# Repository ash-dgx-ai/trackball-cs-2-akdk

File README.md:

# trackball-cs-2

Generated by [Auto-Keyboard-Design-Kit](https://auto-kdk.pages.dev/)

## Preview

- 3D View

- Top View

## Parts List

|Part|Quantity|
|---|---|
|wireless controller|2|
|Conthrough(2.5mm, 9pin)|4|
|Battery|2|
USB-C cable|1|
|MX switch and MX socket|34|
|Diode|34|
|Keycap|34|

## Controller board (reverse-engineered)

The wireless controller board is not included in the original Auto-KDK output.
A reverse-engineered KiCad design compatible with this keyboard is in
[`controller-kicad/`](controller-kicad/README.md).

- 98.0 x 29.0 mm, 2-layer, bottom-side assembly
- Ebyte E73-2G4M08S1C (JLCPCB C356849), MCP73831 4.2V charger, USB-C, PH battery
  connector, trackball FFC, DPDT power switch
- JLCPCB Gerbers/BOM/CPL are included in `controller-kicad/`
- Flash the Adafruit nRF52 UF2 bootloader via the solderless 6-pin 2.54 mm pogo test pads (J4) before use.
- The blank E73 starts at 1.8 V (REGOUT0 default); use a VTref-sensing or level-shifted probe for the first SWD write.

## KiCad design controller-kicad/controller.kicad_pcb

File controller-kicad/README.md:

# AKDK-compatible wireless controller board

Reverse-engineered from the `trackball-cs-2-akdk` repository data
(main-PCB controller footprint, case STL, ZMK `akdk_bt1` DTS, and the
Auto-KDK README).

## Board

- Size: 98.0 x 29.0 mm
- 2 layers, 1.6 mm thickness
- All components are on the **bottom side** (the side opposite the
  conthrough pads). Order JLCPCB PCBA with **Bottom side** assembly.
- Conthrough pads: 2 x 9, 1.27 mm pitch, 19.0 mm row spacing, on the top side.

### Conthrough (KONSHU / コンスルー) mounting

The Conthrough used by this project is the 9-pin, 1.27 mm pitch, H2.5 mm
**through-hole** type (コンスルー 9ピン, 1.27 mm, 高さ2.5 mm). J5 is a 2 x 9
plated-through-hole footprint (0.7 mm drill, 1.1 mm pad, 1.27 mm pitch,
19.0 mm between rows) on the top side. Solder the Conthrough pins into these
holes.

- Hole/pad geometry: 0.7 mm finished hole, 1.1 mm pad, 1.27 mm pitch, 19.0 mm
  row spacing. The 1.1 mm pad leaves 0.17 mm between adjacent pads, above the
  0.1 mm clearance used by this board.
- The pads are plated through-holes, so the Conthrough is mechanically strong.
  Solder on the bottom side (all other components are also on the bottom).
- J5 is excluded from the JLCPCB BOM/CPL; it is a mechanical part. The board
  itself is ordered with the through-holes, so no extra drilling is needed.
- Board thickness is 1.6 mm. Conthrough H2.5 mm is designed for a 1.6 mm board
  plus a 0.9 mm gap; verify the gap to the main PCB after assembly.
- USB-C: 30.85 mm from the left edge, on the top edge. The left case opening
  is centred at x = -18.25 mm, z = -5.75 mm; the connector is horizontally
  centred in the opening. The 3D check shows the connector top is about
  0.17 mm above the case opening top; sand the opening by ~0.2 mm or lower the
  board by ~0.2 mm if it is tight.
- USB-C data: both plug orientations are supported. A6/B6 (D+) and A7/B7
  (D-) are tied with 0.4/0.2 mm via-in-pad and short F.Cu bridges. USB_DM is
  routed manually on F.Cu because Freerouting could not fit both data nets in
  the available corridor. Power, CC and charging also work in both
  orientations. The data vias are inside the 0.3 mm pads; see the JLCPCB
  via-in-pad note below.
- The same board is used for the right half by flipping it over (the main PCB
  SIDE1/SIDE2 variants are different net assignments, not different boards).

## Power / charger

- Li-Po 1S, 3.7 V, with protection circuit, PH 2-pin connector.
- MCP73831 4.2 V single-cell charger (LCSC C14879), 6.2 k PROG resistor
  (~160 mA). The TP4057 was replaced because its 4.24 V termination is above
  the usual 4.20 V Li-Po limit. The charger footprint is a 5-pad SOT-23-5 land
  pattern; PROG is pad 5.
- Charger bypass capacitors: C6/C8 = 10 uF each on VBUS and C7/C9 = 10 uF
  each on VBAT (LCSC C19702, 0603, 10 V), i.e. 20 uF nominal per rail.
  This meets the MCP73831 4.7 uF recommendation even after DC-bias derating;
  verify the effective value at 5 V/4.2 V. C7/C9 are connected to VBAT with
  short B.Cu traces. C8 is at (37.0, 1.8) and C9 at (32.4, 10.0).
- Power switch: DPDT. OFF grounds P0.13 and disconnects the battery; USB then
  powers VDDH through a Schottky diode. Grounding P0.13 is the DFU pin only on
  bootloader builds that use it; see the bootloader section.
- The E73 runs in **high-voltage mode**: VDDH is fed from the battery/USB
  through the Schottky diodes (D1/D2), and VDD is the module's internal 3.3 V
  LDO output (DC/DC disabled, DCCH unconnected). VDD and VDDH are **not**
  tied together on the board; the 3V3 rail is the module's VDD output.
- Battery polarity: J2 pin 1 = +, pin 2 = -. Verify the battery lead polarity
  before plugging it in.
- C3 is 4.7 uF (LCSC C19666, 0603 16 V) on the 3V3/VDD rail. The nRF52840
  VDD decoupling target is 2.7-5.5 uF effective including the E73 module's
  internal capacitors; C3 alone is not the whole sum. Verify the total with
  the E73 module data.
- A blank E73 has REGOUT0 = 1.8 V, so VDD (the 3V3 rail) is 1.8 V until the
  UICR is programmed. After the bootloader/firmware sets REGOUT0 to 3.3 V,
  verify 3.3 V on C3 before connecting the trackball FFC.
- **Battery operation / REG0 dropout**: VDDH = VBAT minus the D2 Schottky
  drop. REG0 regulates 3.3 V only while VDDH is at least about 3.6 V; below
  that it is in dropout and the 3V3 rail follows VDDH (roughly 2.6-3.0 V at
  the battery cutoff). The nRF52840 itself remains within its 1.8-3.6 V
  supply range, and the trackball module's 1.8 V sensor supply should remain
  in regulation, but the 3.3 V rail is not regulated. Measure VDDH/VDD at the
  battery low-voltage cutoff and check the trackball module's minimum VDDIO.
  If the module requires a regulated 3.3 V, add a boost converter (or use a
  higher-voltage supply); otherwise the existing high-voltage/LDO mode is
  acceptable.
- **External 3V3 load**: in high-voltage mode the nRF52840 can supply only
  about 25 mA externally at <=4 dBm (5 mA above 4 dBm, 1 mA in System OFF).
  Measure the trackball module's worst-case current. If it exceeds 25 mA, or
  a regulated 3.3 V is required, add an independent 3.3 V regulator; do not
  rely on the E73 VDD output alone.

## Trackball FFC

The controller-side FFC connector is on the bottom side, while the trackball
module connector is on the opposite side. With a same-side FFC cable the pin
order is reversed. The controller board uses:

| Controller FFC pin | Signal |
|---|---|
| 1 | GND |
| 2 | SCLK (P0.12) |
| 3 | SDIO (P1.09) |
| 4 | MOTION (P0.15) |
| 5 | CS (P0.13) |
| 6 | 3.3 V |

The trackball module's own pinout is 1=3.3V, 2=CS, 3=MOTION, 4=SDIO, 5=SCLK,
6=GND. Verify the cable orientation before soldering/plugging.

## Bootloader / firmware

- The board uses the Adafruit nRF52 UF2 bootloader. Flash it once via the
  solderless 6-pin 2.54 mm pogo test pads (J4). No header or extra parts are
  needed.
- **First SWD connection / REGOUT0**: A blank nRF52840/E73 has
  REGOUT0 = 1.8 V, so VDD and the SWD pins are at 1.8 V. A 3.3 V probe can
  overdrive them. Use a debugger with VTref sensing and level shifting, or a
  1.8 V-compatible probe, for the first write. J4 pad 1 is the target VDD
  sense point; do **not** connect the Pico's 3V3 output to it. For a
  Pico-based first write, use a bidirectional level shifter. TXS0102 is
  auto-direction but must be verified at the SWD clock/load. A single
  74LVC2T45 is **not** suitable: its two channels share DIR, while SWCLK is
  one-way and SWDIO is bidirectional. Use two 74LVC1T45 (one per line) or a
  TXS0102 with VCCA = J4 pad 1 (1.8 V) and VCCB = Pico 3V3, common GND. The
  most reliable option is a debugger with native 1.8 V VTref/level shifting.
- Flash a bootloader build that defines `UICR_REGOUT0_VALUE = 3V3` (for
  example the nice_nano or pillbug build). The bootloader sets REGOUT0 and
  resets; verify 3.3 V on C3. If the chosen build does not set REGOUT0,
  program it via SWD/UICR before using 3.3 V logic. After that, the Pico 2 WH
  3.3 V SWD signals are safe.
- Pogo pad mapping (pad 1 is the pad nearest the top edge; the row is on the
  left edge, 5 mm from the board edge, within the 25 mm clip depth):

  | Pogo pad | Signal | Pico 2 WH connection |
  |---|---|---|
  | 1 | VTref (module VDD sense) | debugger VTref; not Pico 3V3 |
  | 2 | SWDIO | GP3 (level-shifted for the first 1.8 V write) |
  | 3 | SWCLK | GP2 (level-shifted for the first 1.8 V write) |
  | 4 | GND | GND |
  | 5 | RESET (P0.18) | optional; not GP4 by default |
  | 6 | GND | GND |

  The Pico H/2 WH runs the `debugprobe` firmware (SWCLK=GPIO2, SWDIO=GPIO3).
  GP4 is not a guaranteed reset output in all debugprobe builds; leave pad 5
  open unless your probe provides a reset output. Use female-female jumper
  wires; the clip clamps the left board edge, and the 2.54 mm pitch pads are
  2.0 mm diameter with 0.54 mm gaps, so adjacent clip pins do not short.
- **DFU entry**: The power switch OFF grounds P0.13, but that is the DFU
  button only on bootloader builds that define `BUTTON_DFU = P0.13`. The
  nice_nano build has no DFU button and uses the 1200-baud touch instead. If
  OFF + USB does not enter UF2, use the 1200-baud touch (or the reset pad)
  rather than assuming P0.13 works.
- The trackball SPI overlay was changed from `nordic,nrf-spim` to
  `nordic,nrf-spi` as a PAW3222 compatibility precaution; verify on hardware.
  The ZMK left/right build and input test are still pending.
- After the bootloader is flashed, copy the ZMK UF2 built from the
  `trackball-cs-2-akdk` repo.
- The E73-2G4M08S1C exposes all GPIOs used by the `akdk_bt1` DTS except P1.15
  (connector pad 17), which is unused by the firmware. No firmware change is
  required for the matrix/trackball mapping. The module runs in high-voltage
  mode with its internal LDO; DCCH is left unconnected as in the E73 reference
  design.

## JLCPCB order

- Gerbers/drill: `controller_gerbers.zip`
- BOM: `jlcpcb_bom.csv`
- CPL: `jlcpcb_cpl.csv`
- PCB: 98 x 29 mm, 2 layers, 1.6 mm, HASL, default solder mask.
- PCBA: **Bottom side**. The BOM includes the JST PH battery connector and the
  ALPS DPDT switch (THT). JLCPCB THT assembly may be available; otherwise
  hand-solder those two parts. The pogo test pads J4 and the conthrough J5 are
  not in the BOM (J4 is bare copper; J5 is a THT mechanical part). The SWD
  pogo connection is solderless, but J5, J2 and SW1 still require soldering.
- All BOM LCSC parts were in stock at the time of writing:
  - C356849 E73-2G4M08S1C (472)
  - C165948 USB-C TYPE-C-31-M-12 (158981)
  - C14879 MCP73831 (4.2 V charger, in stock)
  - C19702 10uF 0603 10V (C6/C7/C8/C9 charger bypass, in stock)
  - C19666 4.7uF 0603 16V (C3 VDD decoupling, in stock)
  - C131337 JST PH 2P (215233)
  - C202118 FH12-6S-0.5SH (2179)
  - C97434 ALPS SSSS820101 DPDT (2131)
  - C2986031 green LED (20891)
  - C2480 SS14 (1713221)
  - C23186 5.1k, C4260 6.2k, C22976 2M, C22935 1M, C21190 1k, C15849 1uF,
    C14663 0.1uF (all basic/stock)
- **Via-in-pad**: the USB-C D+/D- pads still use 0.4/0.2 mm via-in-pad.
  Moving them outside the 0.3 mm pads conflicts with the CC1/CC2 fan-out, so
  the verified geometry is kept. For the 2-layer JLCPCB order, select the
  **Via in Pad** option (resin-filled and copper-capped, IPC-4761 Type VII)
  and confirm the price/availability; if it is unavailable, the USB-C vias
  must be moved. The P1.06 vias have been moved outside the U1/R6 pads, so
  only the USB-C vias need the special process.
- The CPL rotations are KiCad rotations. Check the JLCPCB placement preview;
  bottom-side rotations may need adjustment. The KiCad **Fabrication Toolkit**
  plugin can generate a JLCPCB-ready CPL if desired.

## DRC

- `kicad-cli pcb drc --severity-error`: **0 violations, 0 unconnected pads,
  0 footprint errors**.
- Run `scripts/set_drc_severity.py` after the PCB pipeline: KiCad rewrites
  the project when a board is saved, which resets courtyard overlaps to
  error. The script keeps them as warnings.
- Full-severity DRC still reports non-electrical warnings: 12 courtyard
  overlaps (bounding boxes; check the 3D preview), silkscreen overlaps/
  clipping, and 15 GND stitching vias that connect only to one pour. The
  stitching vias are intentional; they are not electrically dangling. The
  R3/J2 body overlap was fixed by moving R3 to x=40.5 mm. The C7/J1,
  C8/C9/J1 and C2/U1 overlaps are courtyard-only: the USB-C body ends below
  C7/C9, C8 is clear of C6, and C2's body ends at 80.2 mm while the E73 body
  starts at 80.5 mm. C2 pad 1 overlaps the U1 VDDH pad by design (same net).
- The dense routing splits the B.Cu GND pour into islands. `scripts/stitch_zones.py`
  adds GND stitching vias so every island connects to the main GND; run it
  after `patch_pcb.py` when rebuilding. Skipping it leaves the ground pour
  split.
- The pogo test pads J4 are bare copper pads on the top side, 5 mm from the
  left edge, 2.54 mm pitch, 2.0 mm diameter. They are excluded from BOM/CPL.

## Rebuild

Run with the KiCad AppImage Python (see the scripts for the exact paths):

1. `generate_pcb.py`
2. `route_pcb.py` — assigns nets and imports `controller.ses`. The committed
   session is reused by default so the verified routing is reproducible. Set
   `REROUTE=1` to run Freerouting again; after a fresh route, run
   `export_ses.py` to freeze the new session.
3. `finish_pcb.py` — restores GND and adds the copper pours. Do not import the
   SES here again; `route_pcb.py` already did it.
4. `patch_pcb.py` — USB-C D+/D-, LED/P1.06, C7 VBAT, P0.12 stub, GND stitching.
5. `stitch_zones.py` — connects the remaining GND pour islands.
6. `set_drc_severity.py` — keeps courtyard overlaps as warnings before the
   final DRC report.
7. `update_lcsc.py` is optional; it refreshes the LCSC fields from the table
   above (U2=MCP73831/C14879, C6/C7=C19702).

Then run `kicad-cli pcb drc --severity-error`, and export Gerbers/drill,
BOM/CPL, STEP and PDFs with `kicad-cli` and `generate_bom_cpl.py`.

## Files

- `controller.kicad_pcb` — routed PCB
- `controller.kicad_sch` — block-diagram schematic (global-label connections)
- `controller.kicad_pro` — KiCad project
- `controller_gerbers.zip` — Gerbers + drill files
- `jlcpcb_bom.csv`, `jlcpcb_cpl.csv` — JLCPCB PCBA files
- `controller_sch.pdf`, `controller_pcb_front.pdf`, `controller_pcb_back.pdf`
- `controller.step` — 3D model for case/USB verification
- `controller.pretty/MCP73831_SOT-23-5.kicad_mod` — 5-pad charger footprint (PROG=pad 5)
- `controller.3dshapes/SOT-23-5.wrl`, `controller.3dshapes/SOT-23-5.step`
- `scripts/` — generation/route/BOM/DRC scripts

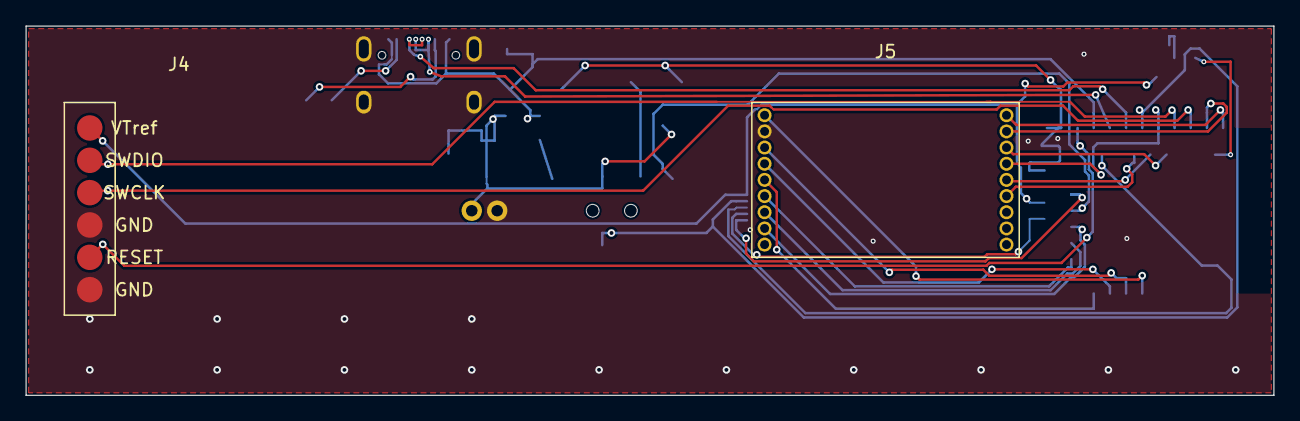
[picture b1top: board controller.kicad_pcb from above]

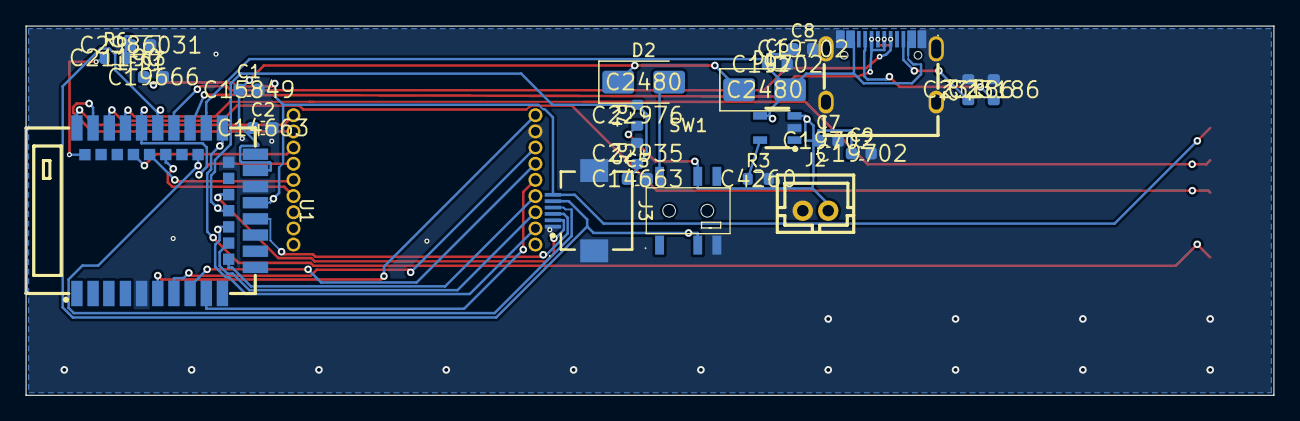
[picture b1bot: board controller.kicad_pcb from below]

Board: 2 copper layers, 98.0 x 29.0 mm, 25 parts (23 on the bottom side), 34 nets.

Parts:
C1: 1uF; C_0603_1608Metric
C2, C5: 0.1uF; C_0603_1608Metric
C3: 4.7uF; C_0603_1608Metric
C6, C7, C8, C9: 10uF; C_0603_1608Metric
D1, D2: SS14; D_SMA
J1: USB-C; USB_C
J2: Battery PH2; JST_PH_2P
J3: FFC 6P 0.5mm; FFC_6P
J4: Pogo test pads; TestPads_6x2.54
J5: Conthrough 2x9 THT; Conthrough_2x9_THT
LED1: Green; LED_0603_1608Metric
R1, R2: 5.1k; R_0603_1608Metric
R3: 6.2k; R_0603_1608Metric
R4: 2M; R_0603_1608Metric
R5: 1M; R_0603_1608Metric
R6: 1k; R_0603_1608Metric
SW1: DPDT; SW_DPDT
U1: E73-2G4M08S1C
U2: MCP73831; MCP73831_SOT-23-5

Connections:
3V3: C3.1, J3.6, J4.1, U1.19
ADC: C5.1, R4.2, R5.1, U1.18
CC1: J1.A5, R1.1
CC2: J1.B5, R2.1
GND: C1.2, C2.2, C3.2, C5.2, C6.2, C7.2, C8.2, C9.2, J1.1, J1.2, J1.3, J1.4, J1.A1B12, J1.B1A12, J2.2, J3.1, J3.7, J3.8, J4.4, J4.6, J5.17, LED1.1, R1.2, R2.2, R3.2, R5.2, SW1.6, U1.5, U1.21, U1.24, U2.2
LED_A: LED1.2, R6.2
P0.02: J5.16, U1.7
P0.06: J5.12, U1.14
P0.08: J5.11, U1.16
P0.09: J5.2, U1.41
P0.10: J5.1, U1.43
P0.12: J3.2, U1.20
P0.13: J3.5, SW1.5, U1.33
P0.15: J3.4, U1.28
P0.18: J4.5, U1.26
P0.20: J5.6, U1.32
P0.22: J5.5, U1.34
P0.24: J5.4, U1.35
P0.26: J5.13, U1.12
P0.29: J5.15, U1.8
P0.31: J5.14, U1.9
P1.00: J5.3, U1.36
P1.06: R6.1, U1.42
P1.09: J3.3, U1.17
P1.13: J5.18, U1.6
PROG: R3.1, U2.5
SWCLK: J4.3, U1.39
SWDIO: J4.2, U1.37
USB_DM: J1.A7, J1.B7, U1.29
USB_DP: J1.A6, J1.B6, U1.31
VBAT: C7.1, C9.1, J2.1, R4.1, SW1.2, U2.3
VBAT_SW: D2.2, SW1.1
VBUS: C6.1, C8.1, D1.2, J1.A4B9, J1.B4A9, U1.27, U2.4
VDDH: C1.1, C2.1, D1.1, D2.1, U1.23

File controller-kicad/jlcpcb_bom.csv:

Comment,Designator,Footprint,LCSC Part #
0.1uF,"C2,C5",C_0603_1608Metric,C14663
10uF,"C6,C7,C8,C9",C_0603_1608Metric,C19702
1M,R5,R_0603_1608Metric,C22935
1k,R6,R_0603_1608Metric,C21190
1uF,C1,C_0603_1608Metric,C15849
2M,R4,R_0603_1608Metric,C22976
4.7uF,C3,C_0603_1608Metric,C19666
5.1k,"R1,R2",R_0603_1608Metric,C23186
6.2k,R3,R_0603_1608Metric,C4260
Battery PH2,J2,JST_PH_2P,C131337
DPDT,SW1,SW_DPDT,C97434
E73-2G4M08S1C,U1,E73-2G4M08S1C,C356849
FFC 6P 0.5mm,J3,FFC_6P,C202118
Green,LED1,LED_0603_1608Metric,C2986031
MCP73831,U2,MCP73831_SOT-23-5,C14879
SS14,"D1,D2",D_SMA,C2480
USB-C,J1,USB_C,C165948

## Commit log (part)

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2025-12-14 Updated keymap.keymap
